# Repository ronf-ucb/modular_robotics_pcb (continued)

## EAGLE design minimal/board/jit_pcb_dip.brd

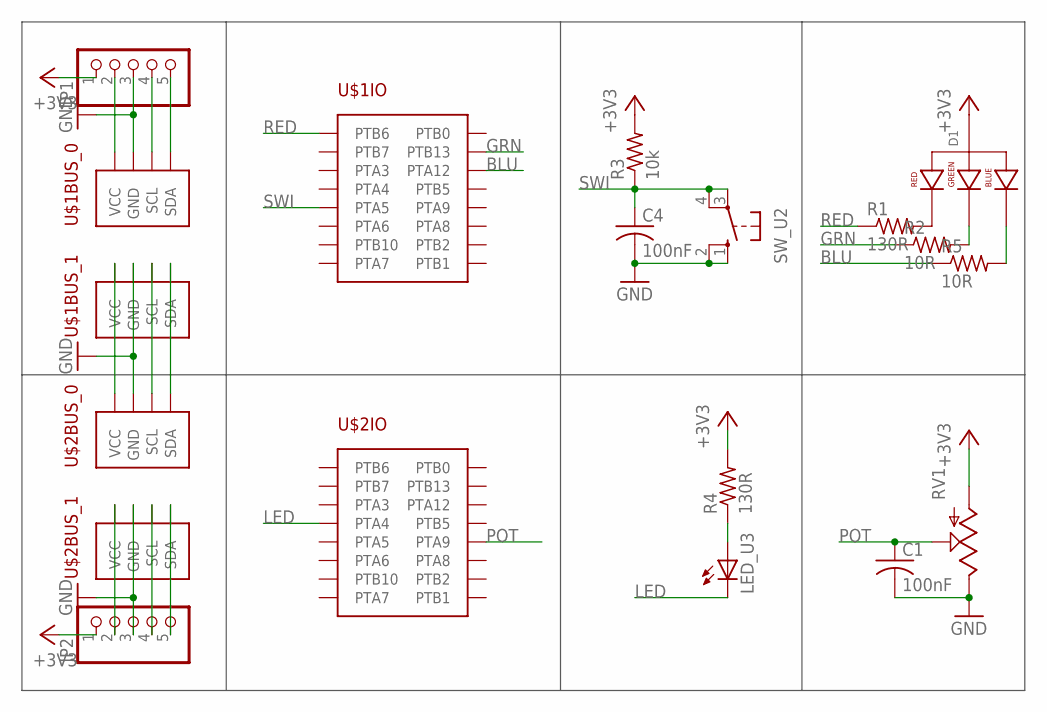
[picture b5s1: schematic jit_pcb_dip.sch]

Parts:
C1, C4: 100nF; C025-025X050
D1: LED-RGB-CA-THRUDIFFUSE; LED-RGB-THRU
JP1, JP2: PINHD-1X5; 1X05
LED_U3: LED5MM
R1, R4: 130R; 0204/7
R2, R5: 10R; 0204/7
R3: 10k; 0204/7
RV1: POT100K_3362U; 3362U
SW_U2: 10-XX; B3F-10XX
U$1, U$2: MODROB_CARRIER-DIP; CARRIER_DIP

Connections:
+3V3: D1.2 (ANODE), JP1.1, JP2.1, R3.2, R4.2, RV1.P$3 (A)
BLU: R5.1, U$1.PTA12
GND: C1.2, C4.2, JP1.3, JP2.3, RV1.P$1 (E), SW_U2.1 (S), SW_U2.2 (S1), U$1.GND_0 (GND), U$1.GND_1 (GND), U$2.GND_0 (GND), U$2.GND_1 (GND)
GRN: R2.1, U$1.PTB13
LED: LED_U3.K (C), U$2.PTA4
unnamed: JP1.2, U$1.VCC_0 (VCC)
unnamed: U$1.VCC_1 (VCC), U$2.VCC_0 (VCC)
unnamed: JP1.4, U$1.SCL_0 (SCL)
unnamed: LED_U3.A, R4.1
unnamed: JP1.5, U$1.SDA_0 (SDA)
unnamed: JP2.2, U$2.VCC_1 (VCC)
unnamed: U$1.SCL_1 (SCL), U$2.SCL_0 (SCL)
unnamed: U$1.SDA_1 (SDA), U$2.SDA_0 (SDA)
unnamed: JP2.4, U$2.SCL_1 (SCL)
unnamed: JP2.5, U$2.SDA_1 (SDA)
unnamed: D1.1 (RED_CATHODE), R1.2
unnamed: D1.3 (GREEN_CATHODE), R2.2
unnamed: D1.4 (BLUE_CATHODE), R5.2
POT: C1.1, RV1.P$2 (S), U$2.PTA9
RED: R1.1, U$1.PTB6
SWI: C4.1, R3.1, SW_U2.3, SW_U2.4 (P1), U$1.PTA5

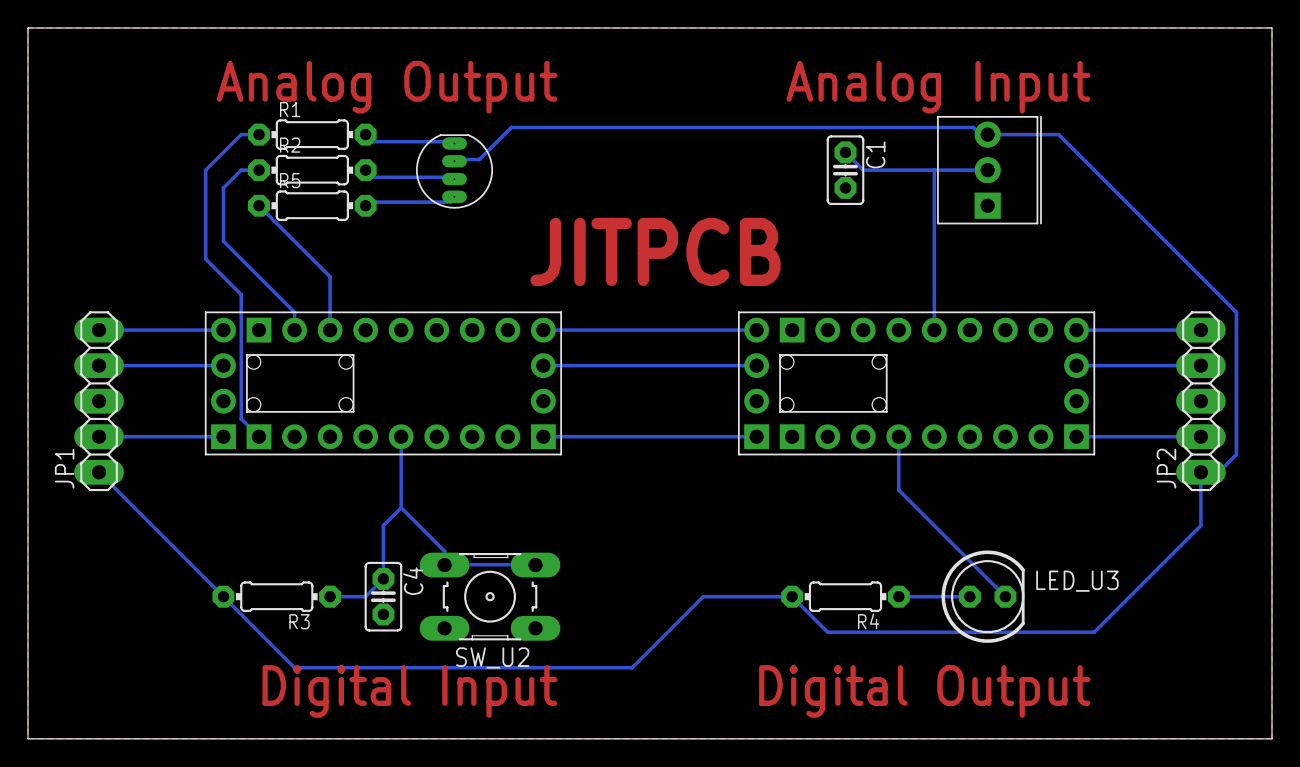
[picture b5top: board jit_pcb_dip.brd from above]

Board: 2 copper layers, 88.9 x 50.8 mm, 15 parts (0 on the bottom side), 21 nets.

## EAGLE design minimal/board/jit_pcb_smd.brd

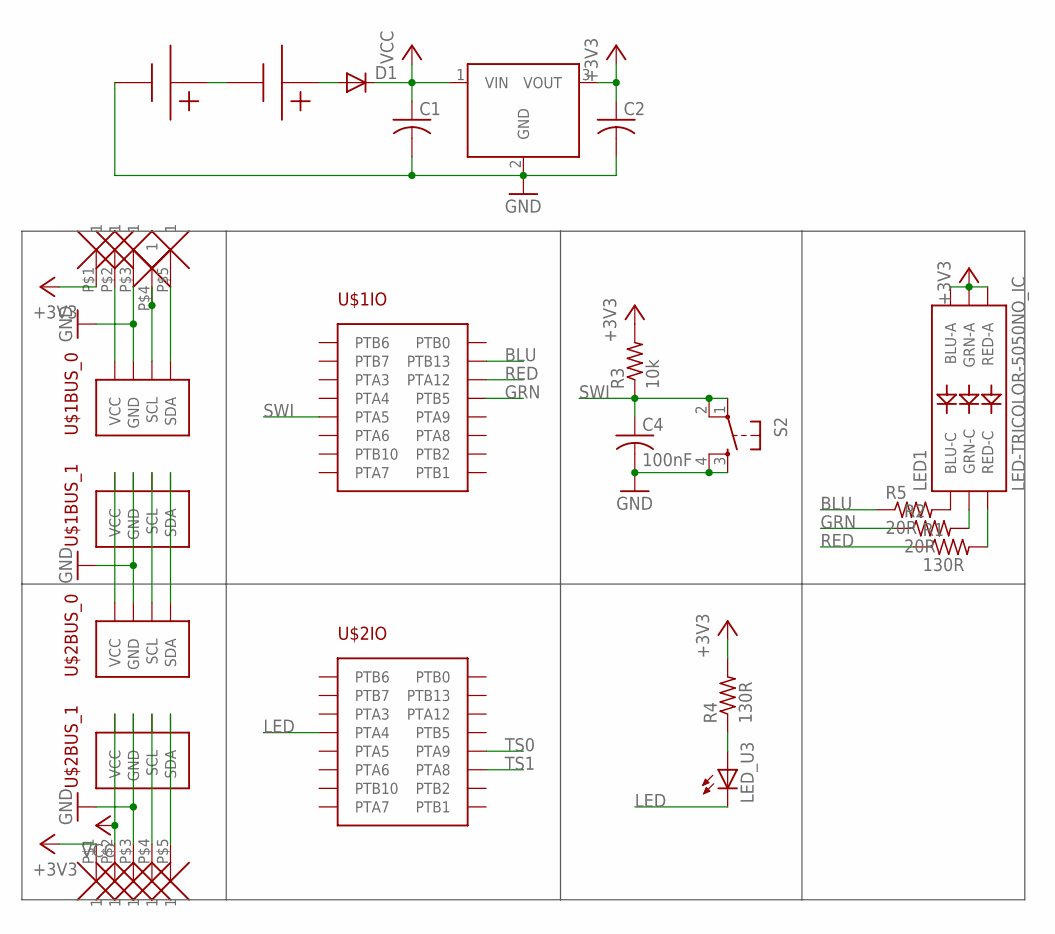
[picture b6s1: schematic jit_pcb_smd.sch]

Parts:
C1, C2: C-USC0805; C0805
C4: 100nF; C0805
D1: DIODE-SMC; SMC
LED1: LED-TRICOLOR-5050NO_IC; LED-TRICOLOR-5050
LED_U3: LEDCHIP-LED0805; CHIP-LED0805
R1, R4: 130R; R0805
R2, R5: 20R; R0805
R3: 10k; R0805
S2: TAC_SWITCHSMD; TACTILE_SWITCH_SMD
U$1, U$2: MODROB_CARRIER-SMD; CARRIER_SMD
U$3, U$4: CR3023; BU2032SM-G
U$5: TC1262; SOT223
U$6, U$7: 1X5_SMD

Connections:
+3V3: C2.1, LED1.1 (GRN-A), LED1.2 (RED-A), LED1.3 (BLU-A), R3.2, R4.2, U$5.3 (VOUT), U$6.P$1, U$7.P$1
BLU: R5.1, U$1.PTB13
GND: C1.2, C2.2, C4.2, S2.3, S2.4, U$1.GND_0 (GND), U$1.GND_1 (GND), U$2.GND_0 (GND), U$2.GND_1 (GND), U$3.-, U$5.2 (GND), U$6.P$3, U$7.P$3
GRN: R2.1, U$1.PTB5
LED: LED_U3.C, U$2.PTA4
unnamed: U$1.VCC_0 (VCC), U$7.P$2
unnamed: U$1.VCC_1 (VCC), U$2.VCC_0 (VCC)
unnamed: U$1.SCL_0 (SCL), U$7.P$4
unnamed: LED_U3.A, R4.1
unnamed: U$1.SDA_0 (SDA), U$7.P$5
unnamed: U$1.SCL_1 (SCL), U$2.SCL_0 (SCL)
unnamed: U$1.SDA_1 (SDA), U$2.SDA_0 (SDA)
unnamed: U$2.SCL_1 (SCL), U$6.P$4
unnamed: U$2.SDA_1 (SDA), U$6.P$5
unnamed: LED1.4 (BLU-C), R5.2
unnamed: LED1.5 (RED-C), R1.2
unnamed: U$3.+, U$4.-
unnamed: LED1.6 (GRN-C), R2.2
unnamed: D1.A, U$4.+
RED: R1.1, U$1.PTA12
SWI: C4.1, R3.1, S2.1, S2.2, U$1.PTA5
TS0: U$2.PTA9
TS1: U$2.PTA8
VCC: C1.1, D1.C, U$2.VCC_1 (VCC), U$5.1 (VIN), U$6.P$2

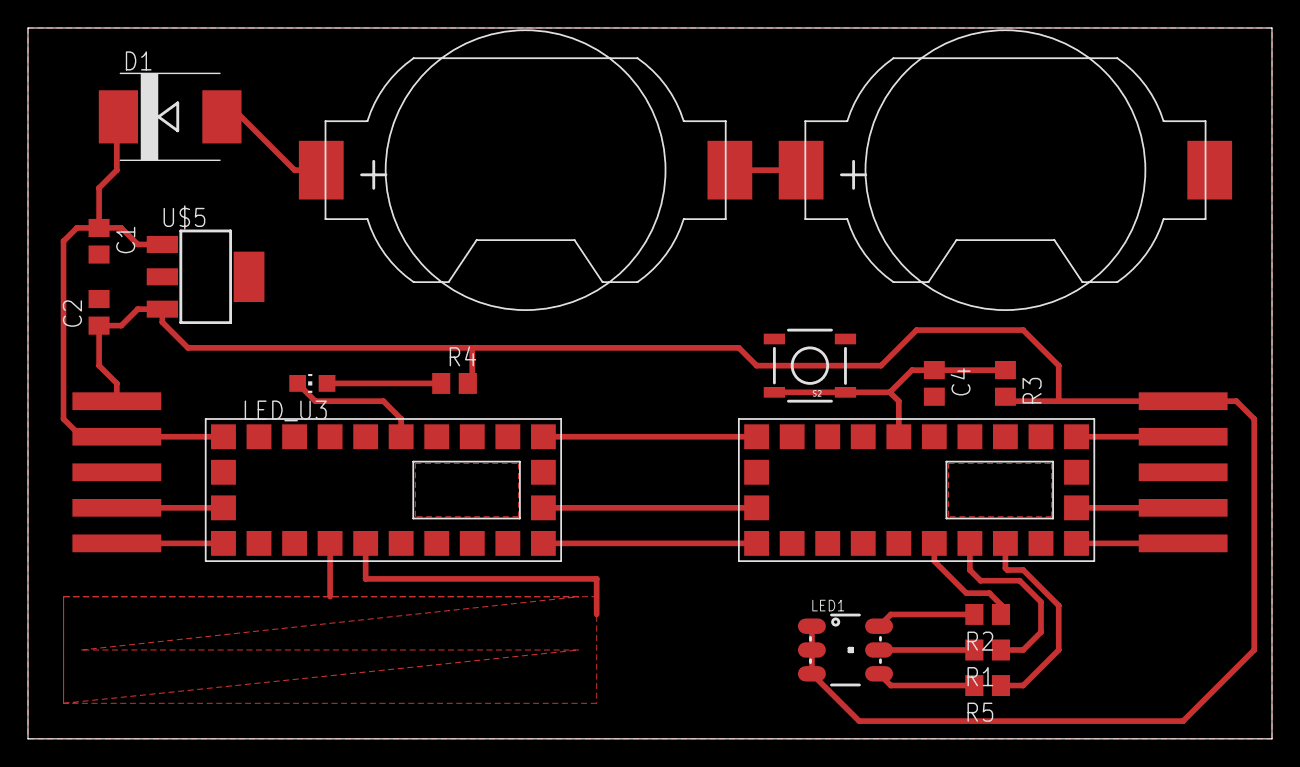
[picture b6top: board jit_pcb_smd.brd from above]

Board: 2 copper layers, 88.9 x 50.8 mm, 19 parts (0 on the bottom side), 22 nets.
